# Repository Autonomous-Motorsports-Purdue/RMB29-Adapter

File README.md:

# RMB29 Adapter
Design for an adapter to allow VESC motor controller to interact with RMB29 sine/cosine motor encoder

## Important/useful links:
- [VESC Sin/Cos Encoder Demo Video](https://www.youtube.com/watch?v=vJPn-aENL2Q)
- [ME1118 Motor Product Page](http://www.motenergy.com/me1118.html)

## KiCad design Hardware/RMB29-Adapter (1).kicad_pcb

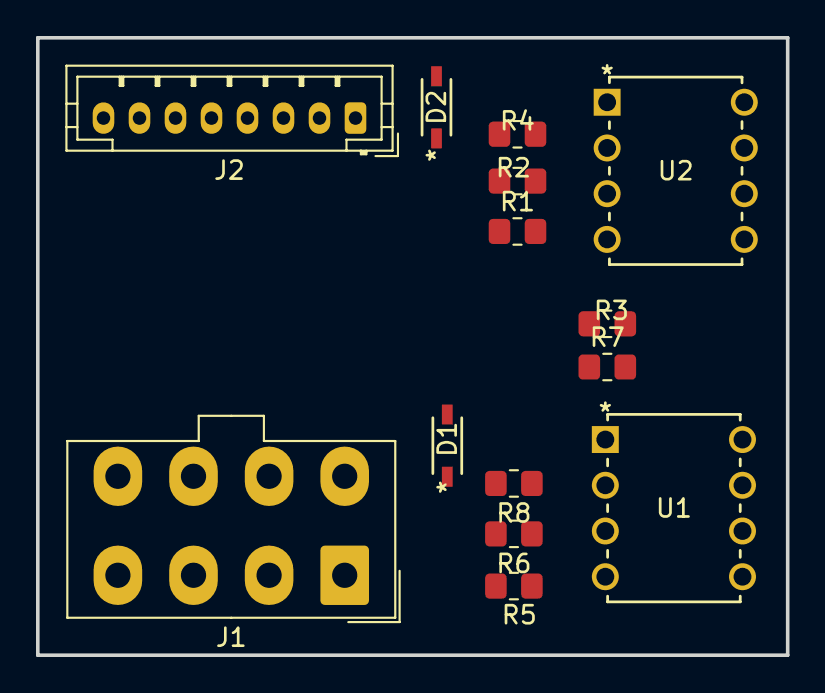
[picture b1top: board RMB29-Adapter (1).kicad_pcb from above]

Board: 2 copper layers, 41.7 x 34.3 mm, 14 parts (0 on the bottom side), 13 nets, no tracks yet.

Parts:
D1, D2: D_Zener; SOD123_DIO
J1: CONN IN; Molex_Mini-Fit_Jr_5566-08A_2x04_P4.20mm_Vertical
J2: CONN OUT; JST_PH_B8B-PH-K_1x08_P2.00mm_Vertical
R1, R5: 1.1K; R_0805_2012Metric_Pad1.20x1.40mm_HandSolder
R2, R3, R6, R7: 10K; R_0805_2012Metric_Pad1.20x1.40mm_HandSolder
R4, R8: 5.1K; R_0805_2012Metric_Pad1.20x1.40mm_HandSolder
U1, U2: MCP602; PDIP8_300MC_MCH

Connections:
+5V: J1.5, J2.5, U2.8 (V+)
/RMB29_COS: J1.2, R5.1
/RMB29_COSOUT: D1.1 (K), J2.2, R8.2, U1.1
/RMB29_COS_DCSCALED: R5.2, R6.1, U1.3 (+)
/RMB29_SIN: J1.1, R1.1
/RMB29_SINOUT: D2.1 (K), J2.1, R4.2, U2.1
/RMB29_SIN_DCSCALED: R1.2, R2.1, U2.3 (+)
/TEMP1: J1.7, J2.7
/TEMP2: J1.8, J2.8
/V+: R3.1, R7.1
GND: J1.3, J1.6, J2.3, J2.6, R2.2, R6.2, U2.4 (V-)
unnamed: R7.2, R8.1, U1.2 (-)
unnamed: R3.2, R4.1, U2.2 (-)

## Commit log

2023-03-22 Remove duplicate file
2023-03-22 Replace TLV272 with MCP602
2023-03-27 Fix offset gain resistors
2023-03-27 Simulation for replacement op-amp circuit
2023-04-17 Remove unused folders
2023-04-17 Add oscilloscope screenshots
2024-04-09 Add files via upload
    Updated Adapter PCB, (zener diode version)
2024-04-09 Add files via upload
    Updated Encoder PCB, (zener version)
2024-04-14 undoing changes to master (2)
2024-04-14 New motor encoder
2024-04-19 Copy project file from master
2024-04-19 Missing connections
